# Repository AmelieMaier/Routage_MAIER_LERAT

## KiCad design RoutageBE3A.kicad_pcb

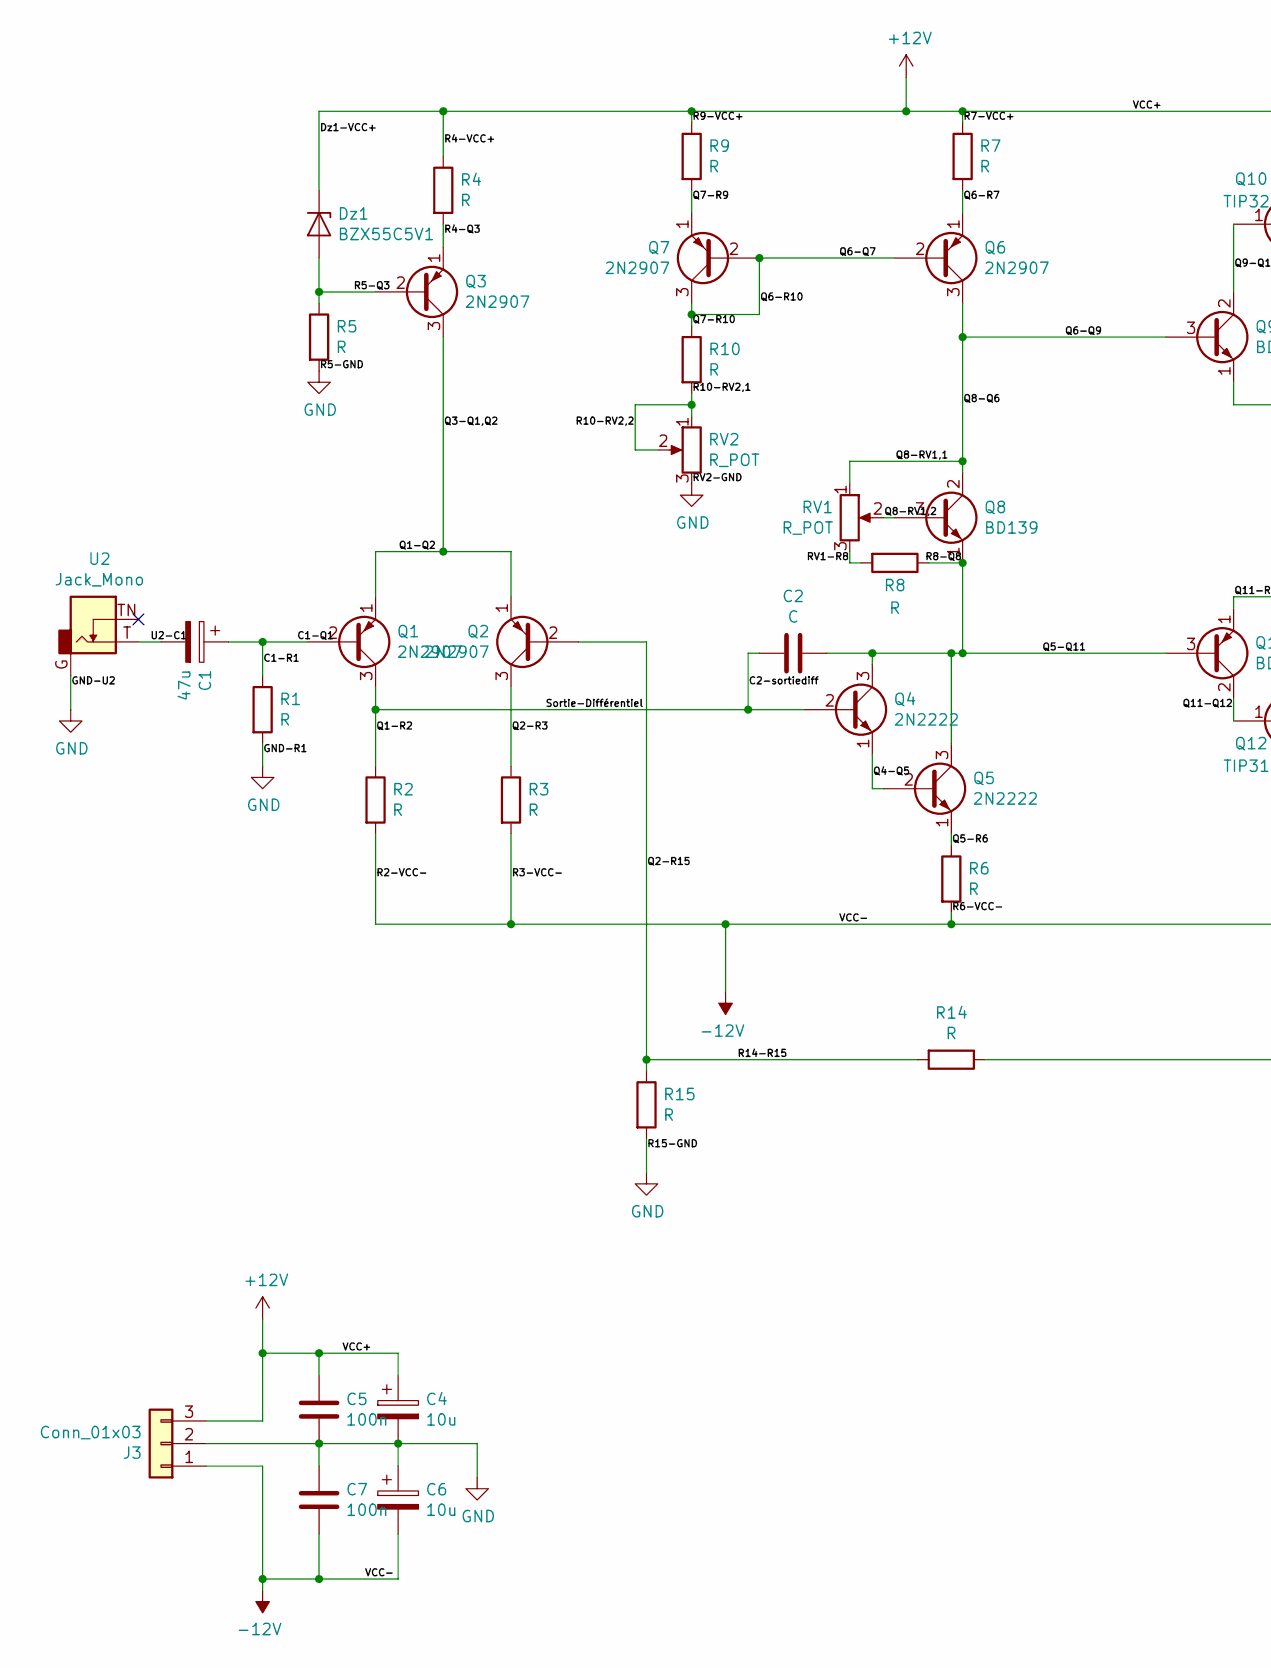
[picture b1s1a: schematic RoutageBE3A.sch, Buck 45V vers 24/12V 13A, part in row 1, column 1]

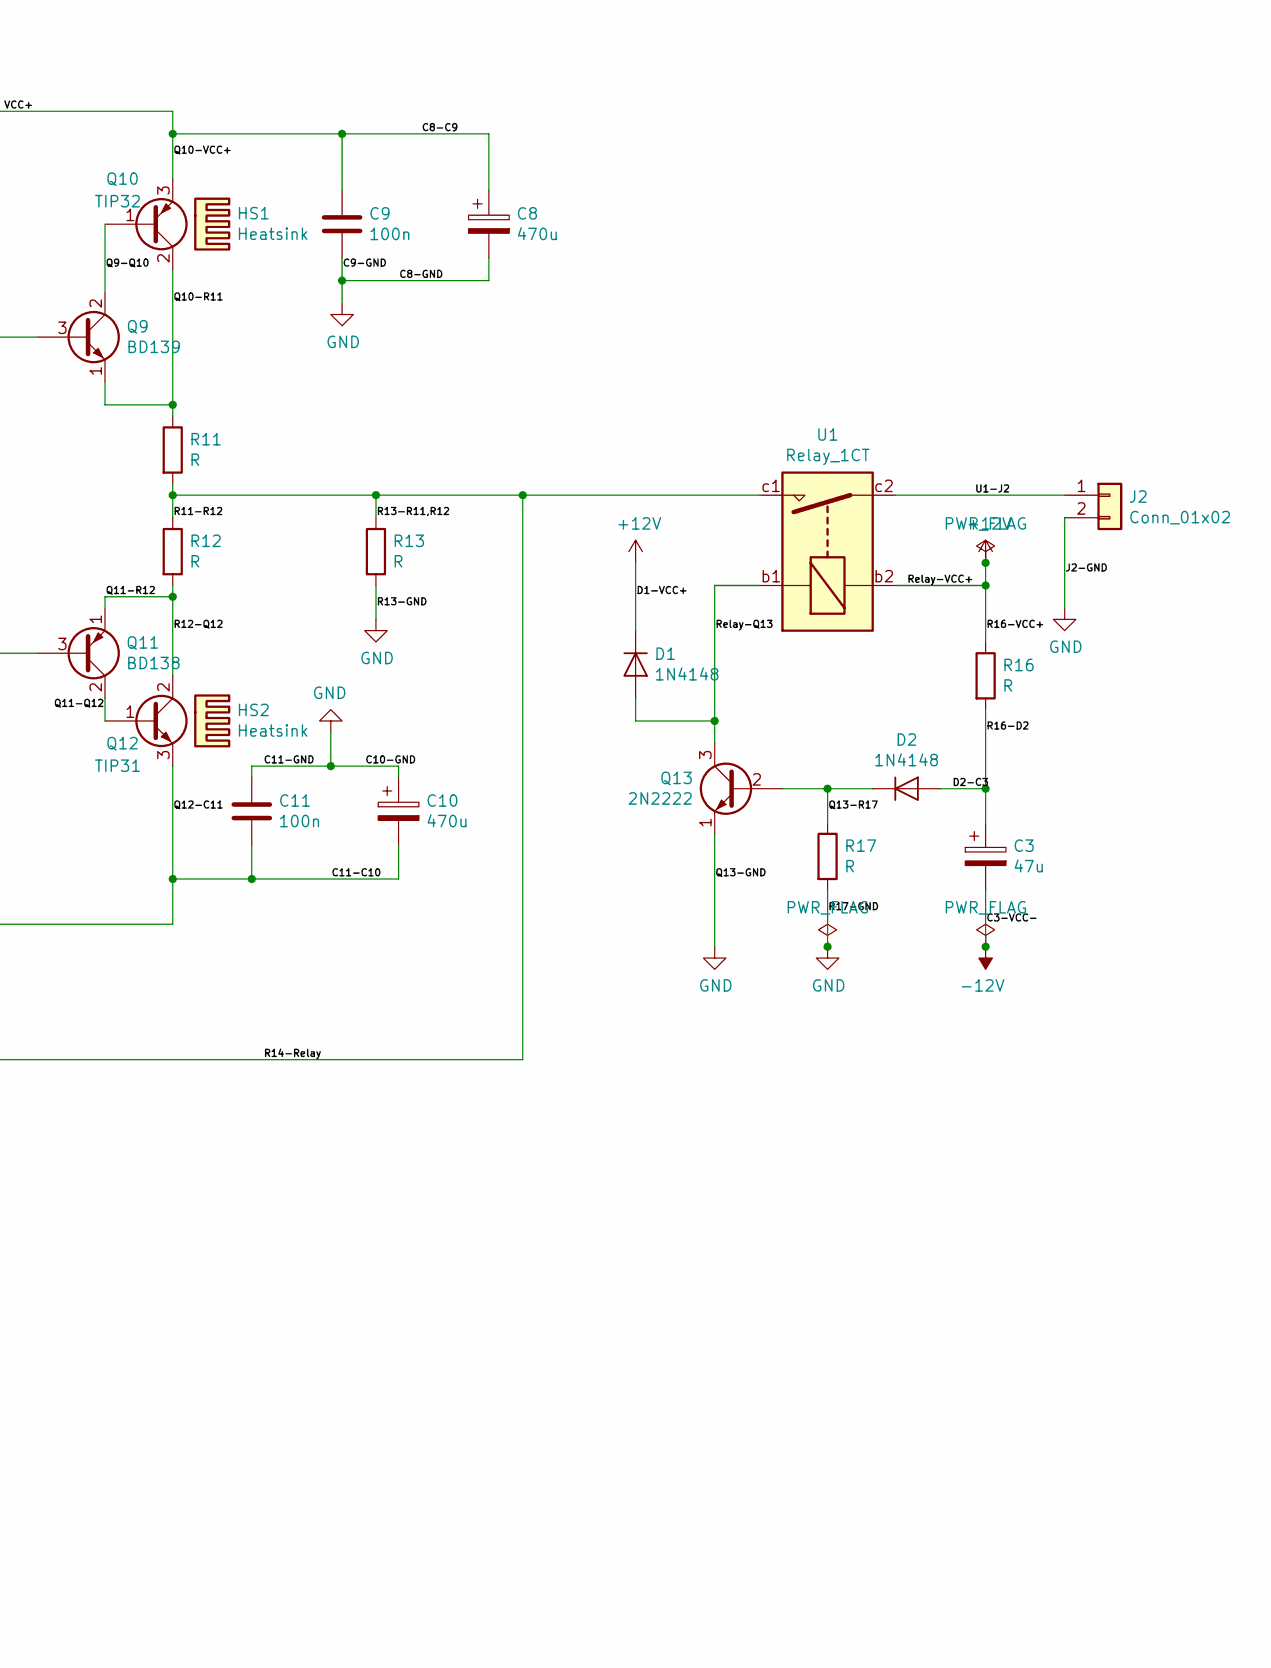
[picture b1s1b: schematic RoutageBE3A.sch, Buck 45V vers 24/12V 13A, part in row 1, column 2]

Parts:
C1, C3: 47u; CP_Radial_D8.0mm_P5.00mm
C2: C; C_Rect_L7.2mm_W3.5mm_P5.00mm_FKS2_FKP2_MKS2_MKP2
C4, C6: 10u; CP_Radial_D8.0mm_P5.00mm
C5, C7, C9, C11: 100n; C_Rect_L7.2mm_W3.5mm_P5.00mm_FKS2_FKP2_MKS2_MKP2
C8, C10: 470u; CP_Radial_D12.5mm_P5.00mm
D1, D2: 1N4148; D_DO-35_SOD27_P10.16mm_Horizontal
Dz1: BZX55C5V1; D_DO-35_SOD27_P10.16mm_Horizontal
HS1, HS2: Heatsink; Heatsink_Fischer_SK104-STC-STIC_35x13mm_2xDrill2.5mm
J2: Conn_01x02; PhoenixContact_MSTBVA_2,5_2-G-5,08_1x02_P5.08mm_Vertical
J3: Conn_01x03; PhoenixContact_MSTBVA_2,5_3-G-5,08_1x03_P5.08mm_Vertical
Q1, Q2, Q3, Q6, Q7: 2N2907; TO-18-3
Q4, Q5, Q13: 2N2222; TO-18-3
Q8, Q9: BD139; TO-126-3_Vertical
Q10: TIP32; TO-220-3_Vertical
Q11: BD138; TO-126-3_Vertical
Q12: TIP31; TO-220-3_Vertical
R1, R2, R3, R4, R5, R6, R7, R8, R9, R10, R13, R14, R15, R16, R17: R; R_Axial_DIN0207_L6.3mm_D2.5mm_P10.16mm_Horizontal
R11, R12: R; R_Axial_DIN0516_L15.5mm_D5.0mm_P20.32mm_Horizontal
RV1, RV2: R_POT; Potentiometer_Bourns_3296W_Vertical
U1: Relay_1CT; Relais_112LMH2
U2: Jack_Mono; Jack_35RAPC2AV

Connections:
+12V: C4.1, C5.1, C8.1, C9.1, D1.1 (K), Dz1.1 (K), J3.3, Q10.3 (E), R4.1, R7.1, R9.1, R16.1, U1.b2
-12V: C3.2, C6.2, C7.2, C10.2, C11.2, J3.1, Q12.3 (E), R2.2, R3.2, R6.2
/C1-Q1: C1.1, Q1.2 (B), R1.1
/C2-sortiediff: C2.1, Q1.3 (C), Q4.2 (B), R2.1
/D2-C3: C3.1, D2.2 (A), R16.2
/Q1-Q2: Q1.1 (E), Q2.1 (E), Q3.3 (C)
/Q2-R3: Q2.3 (C), R3.1
/Q2-R15: Q2.2 (B), R14.2, R15.1
/Q4-Q5: Q4.1 (E), Q5.2 (B)
/Q5-Q11: C2.2, Q4.3 (C), Q5.3 (C), Q8.1 (E), Q11.3 (B), R8.1
/Q5-R6: Q5.1 (E), R6.1
/Q6-Q7: Q6.2 (B), Q7.2 (B), Q7.3 (C), R10.1
/Q6-Q9: Q6.3 (C), Q8.2 (C), Q9.3 (B), RV1.1
/Q6-R7: Q6.1 (E), R7.2
/Q7-R9: Q7.1 (E), R9.2
/Q8-RV1,2: Q8.3 (B), RV1.2
/Q9-Q10: Q9.2 (C), Q10.1 (B)
/Q10-R11: Q9.1 (E), Q10.2 (C), R11.1
/Q11-Q12: Q11.2 (C), Q12.1 (B)
/Q11-R12: Q11.1 (E), Q12.2 (C), R12.2
/Q13-R17: D2.1 (K), Q13.2 (B), R17.1
/R4-Q3: Q3.1 (E), R4.2
/R5-Q3: Dz1.2 (A), Q3.2 (B), R5.1
/R10-RV2,1: R10.2, RV2.1, RV2.2
/R11-R12: R11.2, R12.1, R13.1, R14.1, U1.c1
/RV1-R8: R8.2, RV1.3
/Relay-Q13: D1.2 (A), Q13.3 (C), U1.b1
/U1-J2: J2.1, U1.c2
/U2-C1: C1.2, U2.T
GND: C4.2, C5.2, C6.1, C7.1, C8.2, C9.2, C10.1, C11.1, J2.2, J3.2, Q13.1 (E), R1.2, R5.2, R13.2, R15.2, R17.2, RV2.3, U2.G

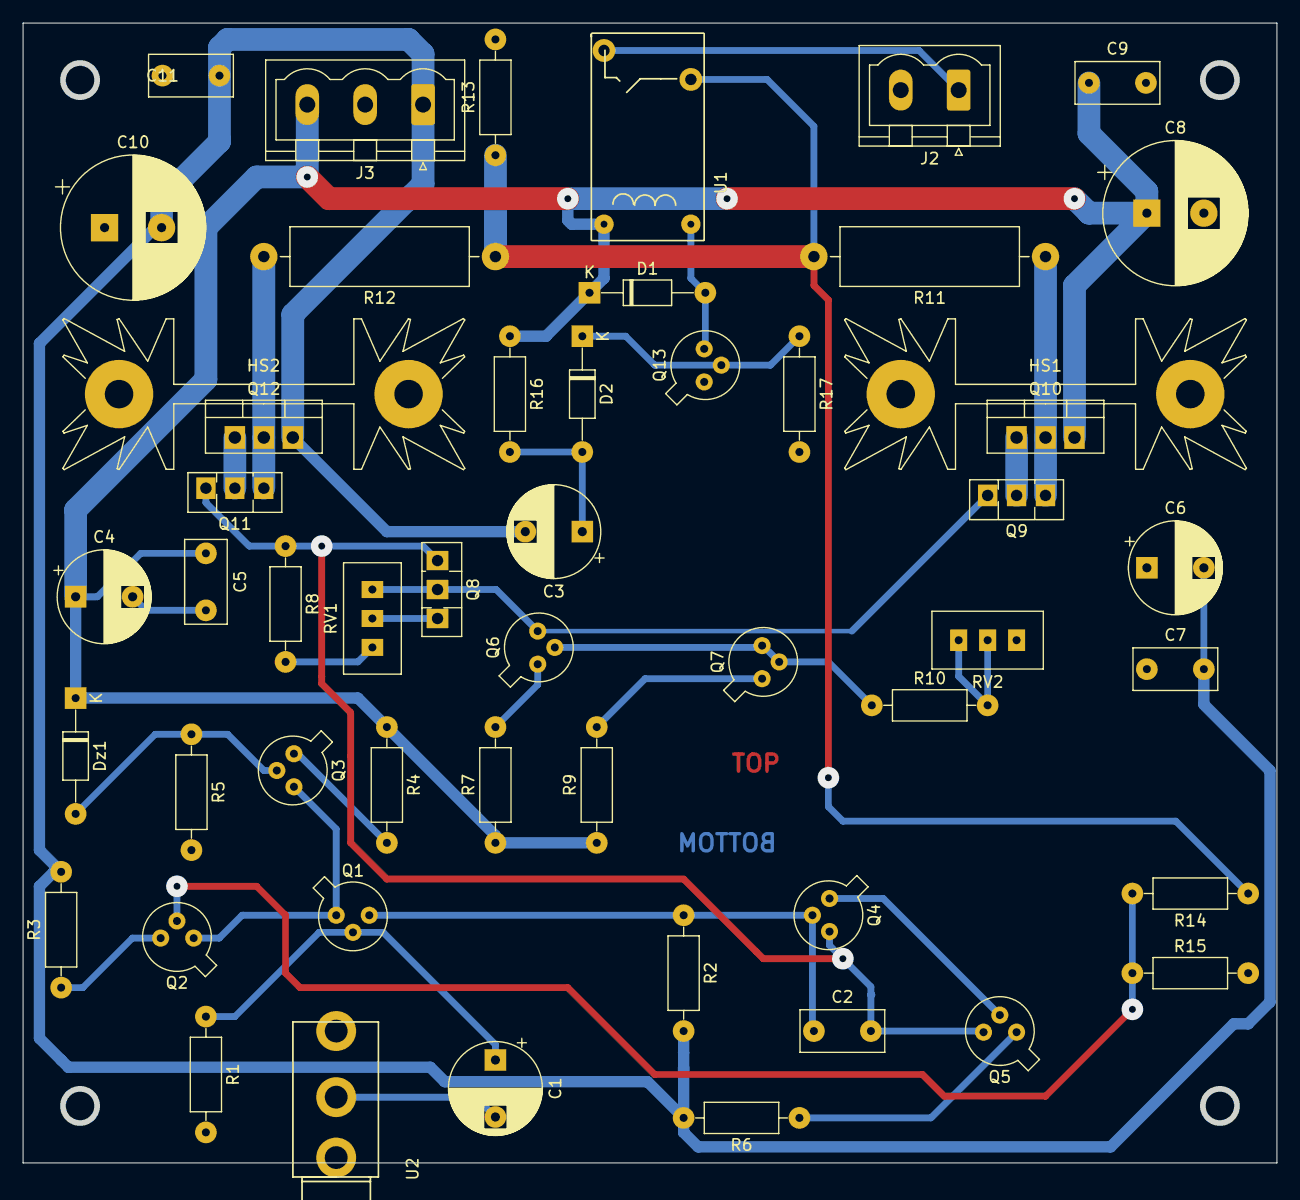
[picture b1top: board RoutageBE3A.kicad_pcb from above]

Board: 2 copper layers, 110.0 x 100.0 mm, 52 parts (0 on the bottom side), 30 nets.

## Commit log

2020-04-12 Added_features
2020-04-13 AddedFeatures
2020-04-15 AvisPlacement
2020-04-15 AvisPlacementOK
2020-04-16 Routage1
2020-04-17 Routage2
2020-04-21 AvisRoutage1
